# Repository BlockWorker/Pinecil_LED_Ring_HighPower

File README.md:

# High-Power Pinecil LED Ring

Inspired by [Herushan's original Pinecil LED ring](https://github.com/Herushan/Pinecil_LED_Ring). See the [full project documentation here](https://blockworker.de/pinecil-led-ring-901/).

This version is designed for three ~0.2W LEDs, resulting in almost 100 lumens of light output.

Features a dedicated LED driver module (to be installed inside the Pinecil case), the LED ring itself, as well as PWM dimming using a [modified version of IronOS](https://github.com/BlockWorker/IronOS-LED).

<center>

</center>

## Build one yourself

Of course, feel free to build your own LED ring based on the designs in this repository. Use them as they are, or modify them for your needs if you feel like it - either way, at your own risk.

The posts on my website offer a more detailed description of the project and [build process that you can follow along with](https://blockworker.de/pinecil-led-ring-build-922/).

The PCB designs are based on JLCPCB's design rules, so adjust them accordingly if you're using a different PCB service. The LED ring PCB is a 1.6mm aluminium core board, and the driver PCB is a 0.8mm 2-layer FR4 board.

Here is a table of the required components, with example parts and Mouser links:

| Reference | Description | Example Part |
| - | - | - |
| U1 | LM3407 LED Driver | [Texas Instruments LM3407MY](https://mou.sr/4eeUAvk) |
| D1 | Schottky Diode, >30V, SOD-323 | [Panjit SS0840WS](https://mou.sr/4a6Dr5q) |
| L1 | Inductor, 150µH, SMD 4 x 4 mm | [Taiyo Yuden NRS4018T151MDGJ](https://mou.sr/3PJLYSF) |
| C1 | Capacitor, 4.7µF 35V, SMD 0805 | [Murata GRM21BZ7YA475KE15](https://mou.sr/3Wa5xai) |
| C2 | Capacitor, 4.7µF 50V, SMD 1206 | [Murata GRM31CR71H475KA12](https://mou.sr/4gZpf0g) |
| C3 | Capacitor, 1µF >6.3V, SMD 0603 | [Samsung CL10B105KA8NNN](https://mou.sr/40pRb75) |
| R1 | Resistor, 4.7kΩ, SMD 0603 | [Bourns CR0603-FX-4701ELF](https://mou.sr/423VuaA) |
| R2 | Resistor, 3.09Ω, SMD 0603 | [Vishay CRCW06033R09FKEA](https://mou.sr/4fNpef5) |
| R3 | Resistor, 1kΩ, SMD 0603 | [Bourns CR0603-FX-1001ELF](https://mou.sr/3VS87BY) |
| R4 | Resistor, 40.2kΩ, SMD 0603 | [Bourns CR0603-FX-4022ELF](https://mou.sr/4h0pGrc) |
| (Ring) D1-D3 | MP-3030-120H LEDs | [Luminus MP-3030-120H-40-90](https://mou.sr/40ogQy9) |

Aside from these parts, you'll need some thin wires, a second soldering iron, and ideally a small PCB hot plate for reflow soldering (especially for soldering the LEDs to the aluminium-core ring PCB). The LM3407 chip also needs either a hot plate or a hot air gun to effectively solder its bottom thermal pad.

Equivalent replacements to these parts should work fine as well - though depending on your choice, you may need to change the PCB component footprints accordingly.

There are many LED options available in the [MP-3030-120H series](https://www.mouser.de/c/?q=mp-3030-120h), depending on your preferences. I went with 4000K colour temperature and CRI 90, for high-quality neutral white light.
Colour temperature options range from very warm 2200K to cold 6500K, and if you want some more brightness at the cost of "light quality", there are brighter CRI 80 variants available.

Of course, there are many other LED options out there that will work, though PCB adjustments may be needed for them. The design targets single-LED chips (around 3V per chip) and a current of 65mA.

If you'd like to use the LED dimming feature, you need to flash my [modified IronOS firmware](https://github.com/BlockWorker/IronOS-LED) onto your Pinecil and connect the "DIM" pad to the Pinecil PCB as shown on my website.
Alternatively, you can just force the ring to 100% brightness all the time, by connecting a jumper wire between the "DIM" pad and the "TP1" test point on the back side of the driver.

The driver circuit can be modified for up to 350mA LED current (see notes in the schematic and the [LM3407 datasheet](https://www.ti.com/lit/ds/symlink/lm3407.pdf)), but I haven't tested higher currents, and LED cooling may become a problem at higher power.

If you'd like to make the ring removable ([as seen on my website](https://blockworker.de/pinecil-led-ring-build-922/)), you'll need a very small 2-pin connector, e.g., the [Amphenol Minitek 0.8mm connector I used](https://www.amphenol-cs.com/product-series/minitek-0-80mm-wtb.html#). The header can be wired to the ring and glued onto its back using some epoxy. However, crimping the wire end of such a small connector is challenging - [I've made a post about my process for it here](https://blockworker.de/modular-audio-appendix-minitek-0-8mm-connectors-2055/). I don't recommend this for beginners though.

For questions or anything else, you can find me on the official PINE64 discord server (@blockworker).

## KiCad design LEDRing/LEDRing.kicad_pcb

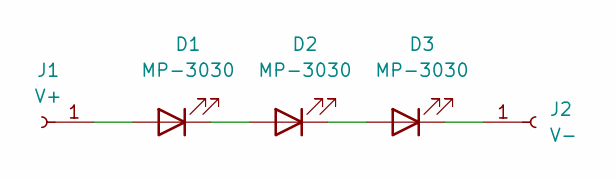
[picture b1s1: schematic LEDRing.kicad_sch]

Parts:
D1, D2, D3: MP-3030; LED_Luminus_MP-3030-1100_3.0x3.0mm
J1: V+; SolderWirePad_1x01_SMD_1x2mm
J2: V-; SolderWirePad_1x01_SMD_1x2mm

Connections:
unnamed: D1.2 (A), J1.1
unnamed: D1.1 (K), D2.2 (A)
unnamed: D2.1 (K), D3.2 (A)
unnamed: D3.1 (K), J2.1

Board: 2 copper layers, 6 parts (0 on the bottom side), 4 nets, no tracks yet.

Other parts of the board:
Logo: BW_Logo_Silk_5x3.2mm

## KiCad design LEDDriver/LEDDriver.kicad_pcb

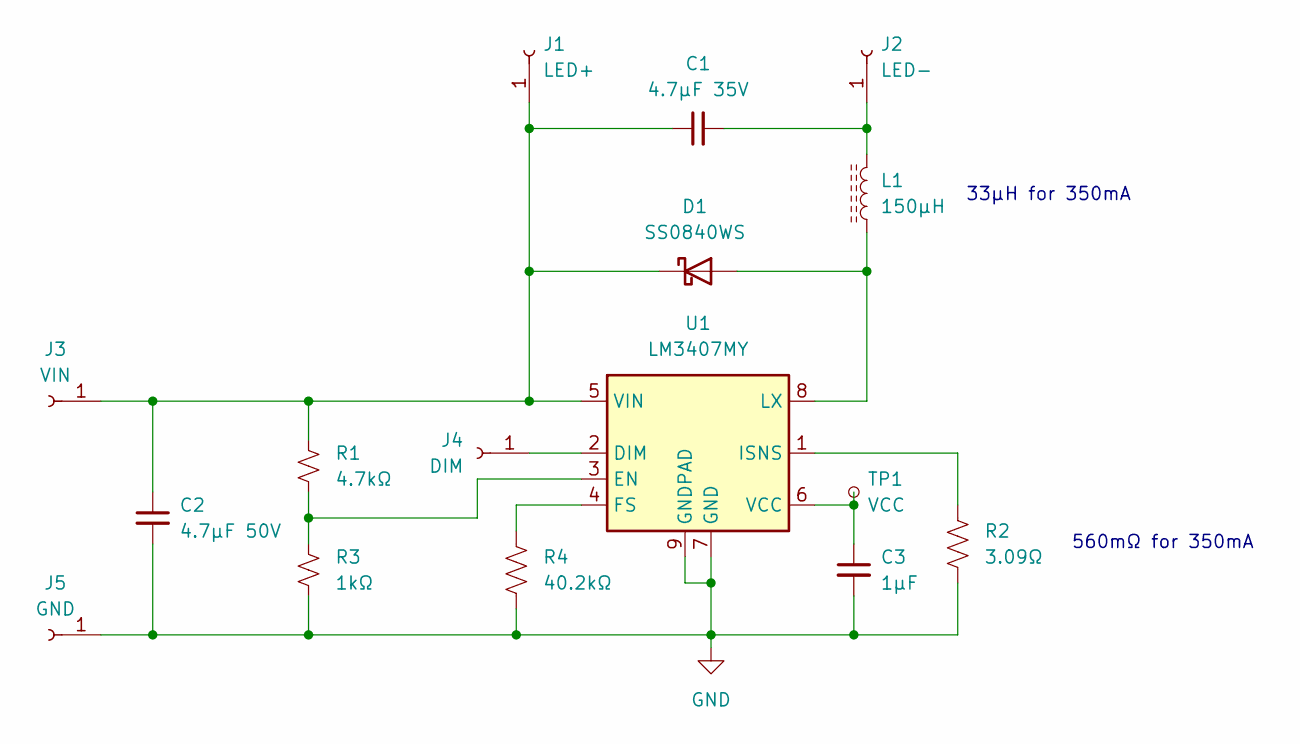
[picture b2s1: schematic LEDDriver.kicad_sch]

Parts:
C1: 4.7µF 35V; C_0805_2012Metric
C2: 4.7µF 50V; C_1206_3216Metric
C3: 1µF; C_0603_1608Metric
D1: SS0840WS; D_SOD-323_HandSoldering
J1: LED+; SolderWire-0.5sqmm_1x01_D0.9mm_OD2.1mm
J2: LED-; SolderWire-0.5sqmm_1x01_D0.9mm_OD2.1mm
J3: VIN; SolderWire-0.5sqmm_1x01_D0.9mm_OD2.1mm
J4: DIM; SolderWire-0.5sqmm_1x01_D0.9mm_OD2.1mm
J5: GND; SolderWire-0.5sqmm_1x01_D0.9mm_OD2.1mm
L1: 150µH; L_Taiyo-Yuden_NR-40xx_HandSolderingCompact
R1: 4.7kΩ; R_0603_1608Metric
R2: 3.09Ω; R_0603_1608Metric
R3: 1kΩ; R_0603_1608Metric
R4: 40.2kΩ; R_0603_1608Metric
TP1: VCC; TestPoint_Pad_D1.0mm
U1: LM3407MY; MSOP-8-1EP_3x3mm_P0.65mm_EP1.73x1.85mm

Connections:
GND: C2.2, C3.2, J5.1, R2.2, R3.2, R4.2, U1.7 (GND), U1.9 (GNDPAD)
unnamed: D1.2 (A), L1.1, U1.8 (LX)
unnamed: C1.1, C2.1, D1.1 (K), J1.1, J3.1, R1.1, U1.5 (VIN)
unnamed: C1.2, J2.1, L1.2
unnamed: J4.1, U1.2 (DIM)
unnamed: R1.2, R3.1, U1.3 (EN)
unnamed: R4.1, U1.4 (FS)
unnamed: R2.1, U1.1 (ISNS)
unnamed: C3.1, TP1.1, U1.6 (VCC)

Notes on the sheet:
33µH for 350mA
560mΩ for 350mA

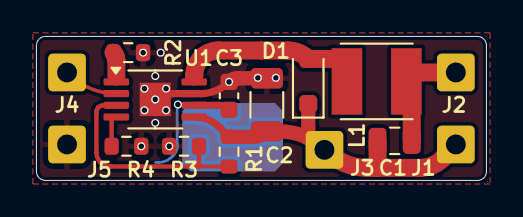
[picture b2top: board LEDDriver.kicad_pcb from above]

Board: 2 copper layers, 25.0 x 8.0 mm, 16 parts (1 on the bottom side), 9 nets.

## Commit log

2024-10-26 Create LICENSE
2024-10-26 Inventory done
2025-01-06 Ring hole size increased
2025-01-06 Extended README
2025-01-06 Readme update

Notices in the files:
parts and their libraries:
©2024 BlockWorker
